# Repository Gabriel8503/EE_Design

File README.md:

# ⚡ EE_Design

Welcome to my Electrical Engineering design repository. This space is dedicated to documenting my journey as I build, test, and refine custom circuitry—from concept to production.

## 📘 Purpose

This repo will serve as a running log of my EE projects, experiments, and useful resources I reference or study during the process.

## 🛠️ Current Focus

- Designing microcontroller-based boards from scratch  
- Understanding and applying best practices in PCB design  
- Learning embedded systems and firmware workflows  

## 📚 Resources

Here's a curated list of resources that I'm currently using:

- **Getting to Blinky 5.0**  
  *(A foundational project series for FPGA and PCB design by Chris Gammell)*

- **Building a Microcontroller Board from Scratch**  
  [PDF ](https://attachments.convertkitcdnm.com/131144/1861af26-d50b-4f31-98b9-467ac304307f/Building-a-Microcontroller-Board-from-Scratch.pdf?utm_campaign=Landing%20Page%20or%20Form%20-%20939283&utm_medium=email&utm_source=convertkit)  
  *(Comprehensive walkthrough of the full design-to-manufacturing pipeline)*

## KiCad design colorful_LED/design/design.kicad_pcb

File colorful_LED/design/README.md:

# PCB Design Documentation

## Schematic
Below is the latest schematic snapshot for reference:  

## PCB Layout
Below is the latest PCB layout snapshot for reference:

### Front 

### Back

## Design Notes
- **Software Used:** KiCad  
- **Board Specs :**
  - Dimensions (mm): 66.5 x 60
  - Layer count: 4
  - Power requirements: 3V Cell Battery / USB

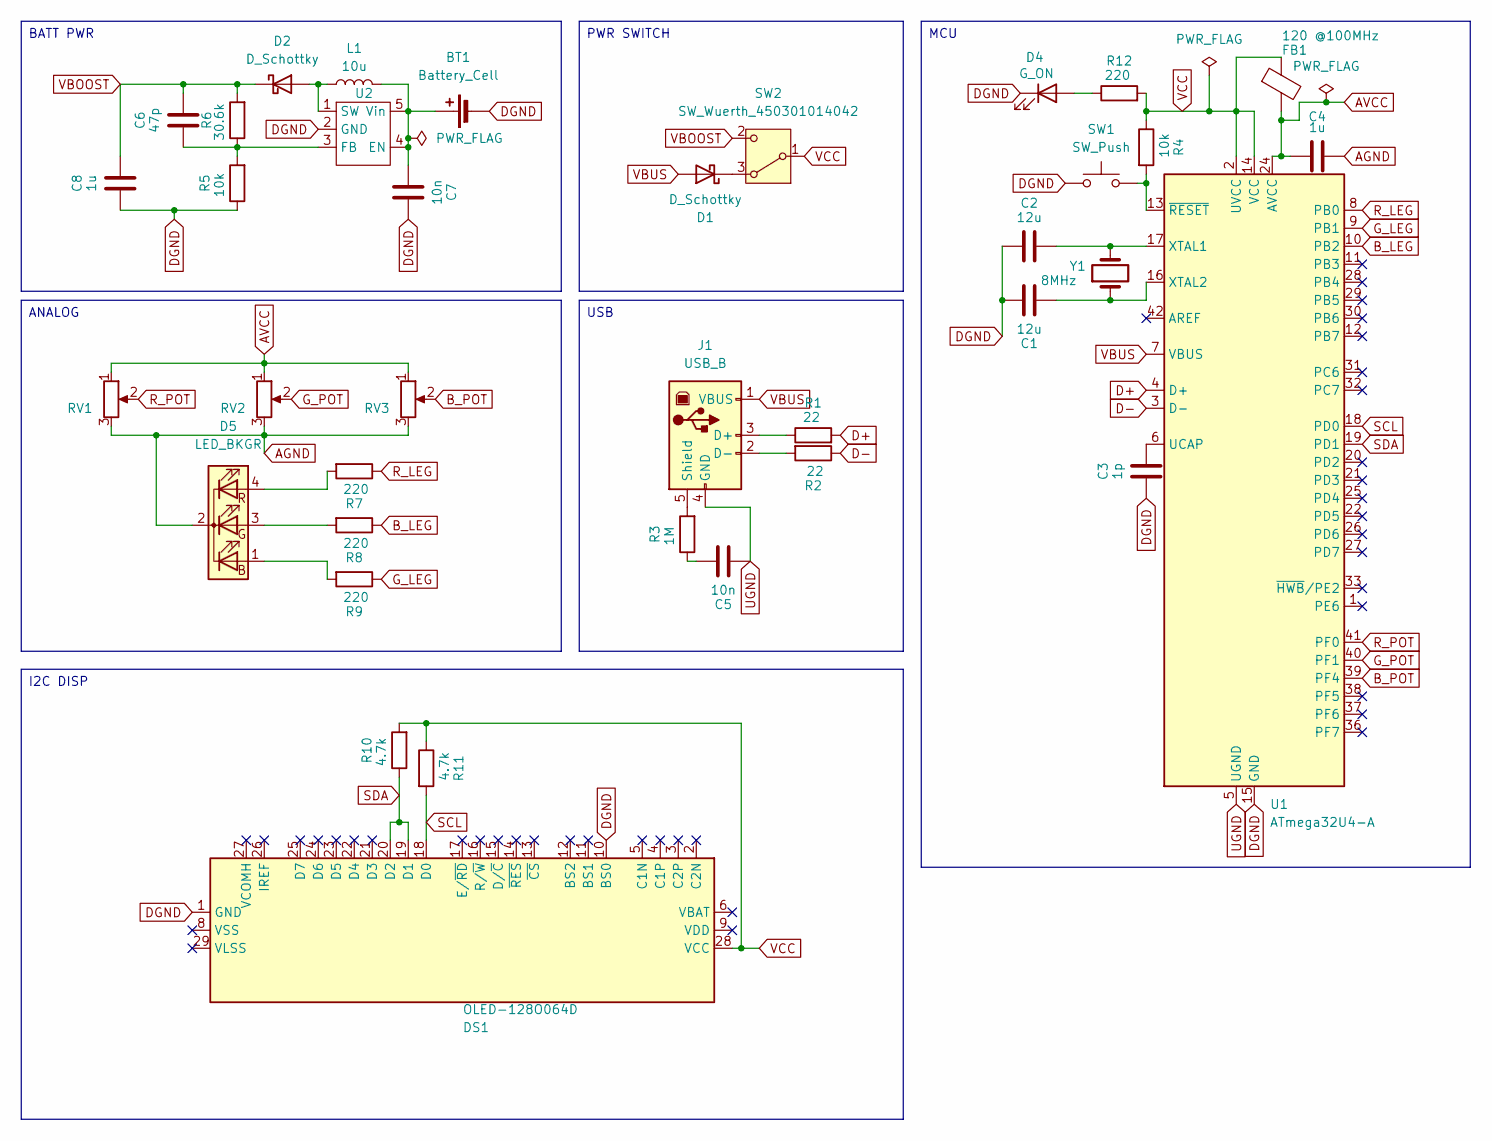
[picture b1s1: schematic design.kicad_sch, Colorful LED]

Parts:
BT1: Battery_Cell; BatteryHolder_ComfortableElectronic_CH273-2450_1x2450
C1, C2: 12u; C_0805_2012Metric
C3: 1p; C_0805_2012Metric
C4, C8: 1u; C_0805_2012Metric
C5, C7: 10n; C_0805_2012Metric
C6: 47p; C_0805_2012Metric
D1, D2: D_Schottky; D_0805_2012Metric
D4: G_ON; LED_0805_2012Metric
D5: LED_BKGR; LED_D5.0mm-4_RGB
DS1: OLED-128O064D
FB1: 120 @100MHz; L_0603_1608Metric_Pad1.05x0.95mm_HandSolder
J1: USB_B; USB_B_Lumberg_2411_02_Horizontal
L1: 10u; L_0805_2012Metric
R1, R2: 22; R_0805_2012Metric
R3: 1M; R_0805_2012Metric
R4, R5: 10k; R_0805_2012Metric
R6: 30.6k; R_0805_2012Metric
R7, R8, R9, R12: 220; R_0805_2012Metric
R10, R11: 4.7k; R_0805_2012Metric
RV1, RV2, RV3: R_Potentiometer; Potentiometer_Bourns_3314S_Horizontal
SW1: SW_Push; SW_Push_1TS009xxxx-xxxx-xxxx_6x6x5mm
SW2: SW_Wuerth_450301014042; SW_Slide-03_Wuerth-WS-SLTV_10x2.5x6.4_P2.54mm
U1: ATmega32U4-A; TQFP-44_10x10mm_P0.8mm
U2: Reg
Y1: 8MHz; Crystal_SMD_HC49-SD_HandSoldering

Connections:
AGND: C4.1, D5.2 (K), RV1.3, RV2.3, RV3.3
AVCC: C4.2, FB1.2, RV1.1, RV2.1, RV3.1, U1.24 (AVCC), U1.44 (AVCC)
B_LEG: R8.1, U1.10 (PB2)
B_POT: RV3.2, U1.39 (PF4)
D+: R1.2, U1.4 (D+)
D-: R2.1, U1.3 (D-)
DGND: BT1.2 (-), C1.1, C2.1, C3.2, C7.1, C8.2, D4.1 (K), DS1.1 (GND), DS1.10 (BS0), DS1.30 (GND), R5.1, SW1.1, U1.15 (GND), U1.23 (GND), U1.35 (GND), U1.43 (GND), U2.2 (GND)
G_LEG: R9.1, U1.9 (PB1)
G_POT: RV2.2, U1.40 (PF1)
unnamed: BT1.1 (+), C7.2, L1.2, U2.4 (EN), U2.5 (Vin)
unnamed: C5.1, R3.1
unnamed: D1.1 (K), SW2.3 (A)
unnamed: D2.2 (A), L1.1, U2.1 (SW)
unnamed: D4.2 (A), R12.1
unnamed: D5.1 (BA), R9.2
unnamed: D5.3 (GA), R8.2
unnamed: D5.4 (RA), R7.2
unnamed: J1.3 (D+), R1.1
unnamed: J1.2 (D-), R2.2
unnamed: J1.5 (Shield), R3.2
unnamed: C3.1, U1.6 (UCAP)
unnamed: C2.2, U1.17 (XTAL1), Y1.2
unnamed: C1.2, U1.16 (XTAL2), Y1.1
unnamed: R4.2, SW1.2, U1.13 (~RESET)
unnamed: C6.2, R5.2, R6.1, U2.3 (FB)
R_LEG: R7.1, U1.8 (PB0)
R_POT: RV1.2, U1.41 (PF0)
SCL: DS1.18 (D0), R11.2, U1.18 (PD0)
SDA: DS1.19 (D1), DS1.20 (D2), R10.1, U1.19 (PD1)
UGND: C5.2, J1.4 (GND), U1.5 (UGND)
VBOOST: C6.1, C8.1, D2.1 (K), R6.2, SW2.2 (C)
VBUS: D1.2 (A), J1.1 (VBUS), U1.7 (VBUS)
VCC: DS1.28 (VCC), FB1.1, R4.1, R10.2, R11.1, R12.2, SW2.1 (B), U1.2 (UVCC), U1.14 (VCC), U1.34 (VCC)

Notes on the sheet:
BATT PWR
I2C DISP
PWR SWITCH
ANALOG
USB
MCU

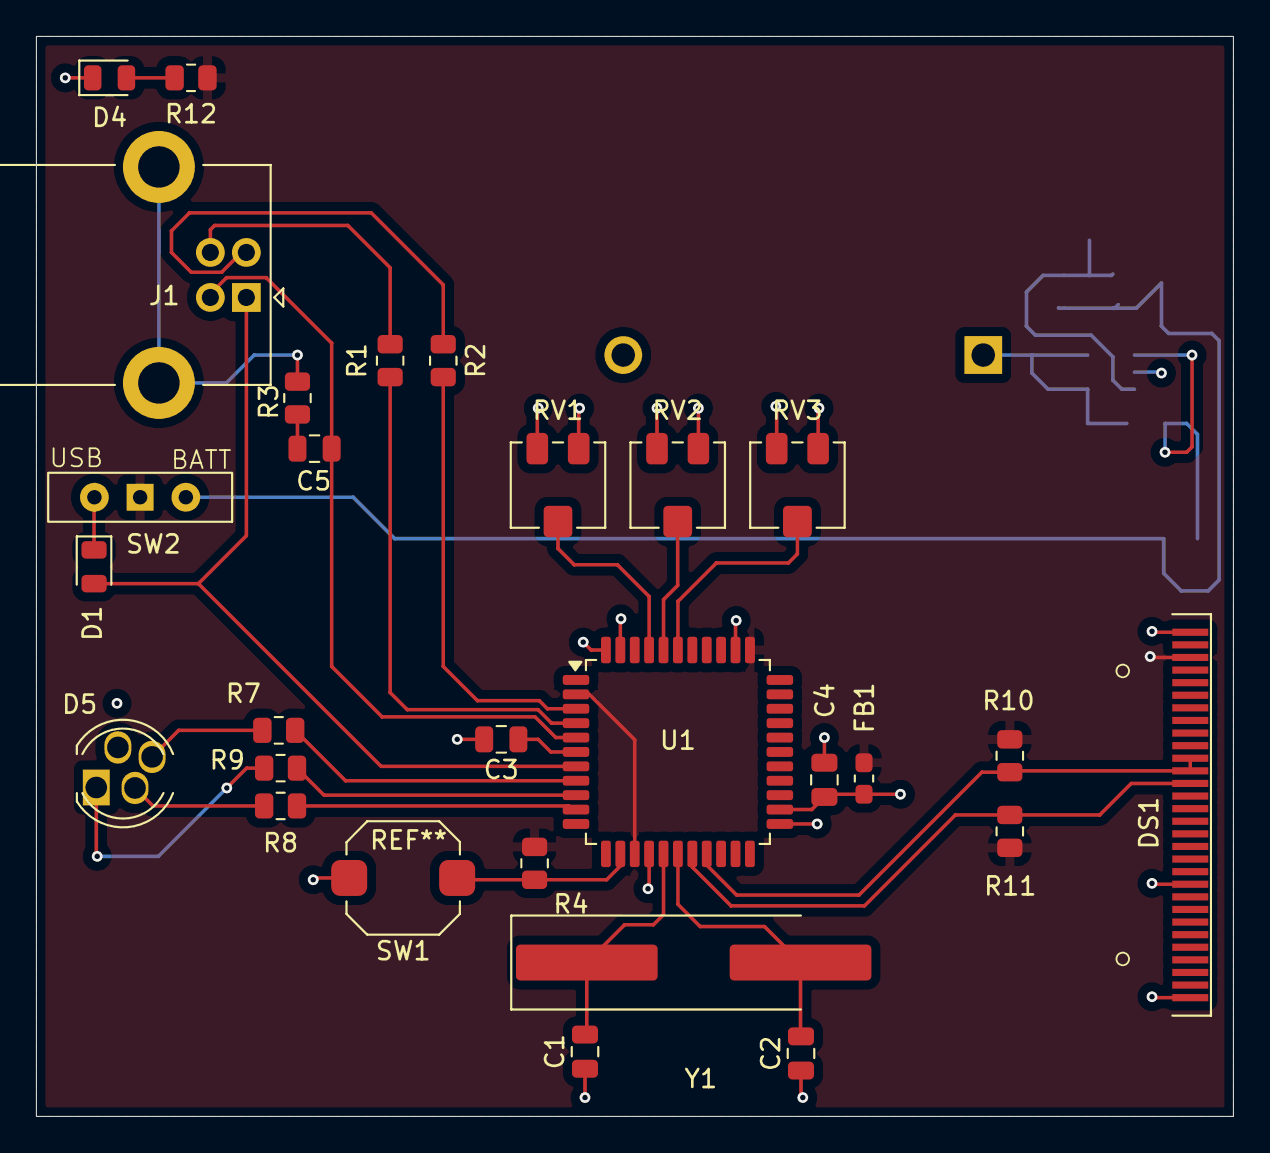
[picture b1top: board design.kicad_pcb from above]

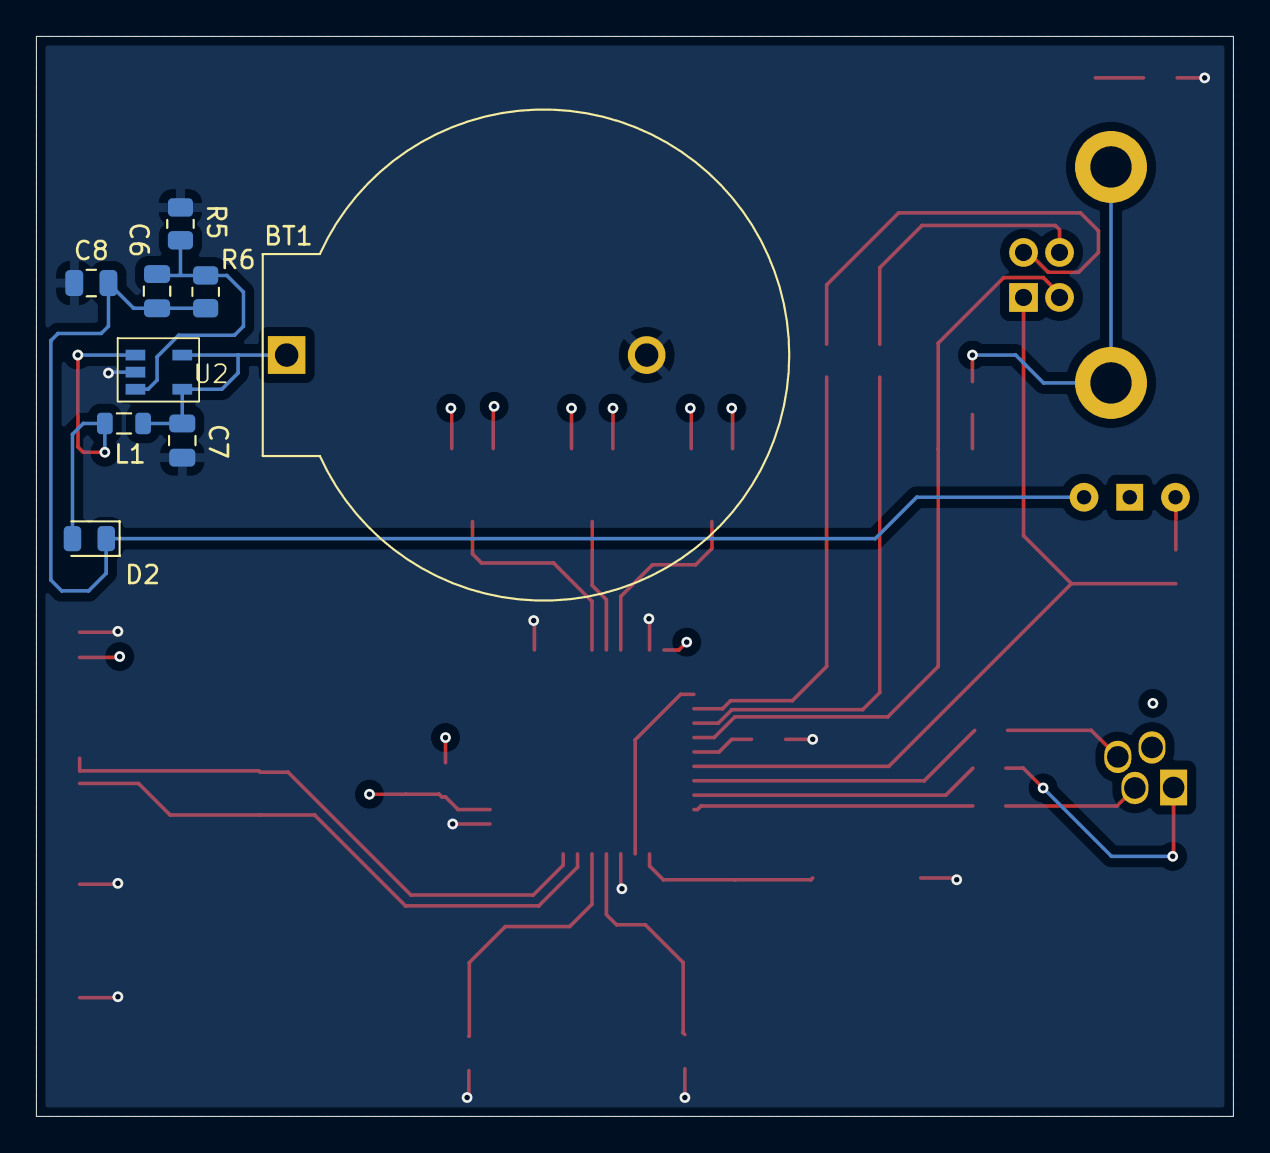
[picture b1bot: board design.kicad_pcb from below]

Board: 4 copper layers, 66.5 x 60.0 mm, 37 parts (9 on the bottom side), 33 nets.

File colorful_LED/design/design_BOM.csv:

"Reference","Qty","Value","DNP","Exclude from BOM","Exclude from Board","Footprint","Datasheet"
"BT1","1","Battery_Cell","","","","Battery:BatteryHolder_ComfortableElectronic_CH273-2450_1x2450","~"
"C1,C2","2","12u","","","","","~"
"C3","1","1p","","","","Capacitor_SMD:C_0805_2012Metric","~"
"C4,C8","2","1u","","","","Capacitor_SMD:C_0805_2012Metric","~"
"C5,C7","2","10n","","","","Capacitor_SMD:C_0805_2012Metric","~"
"C6","1","47p","","","","Capacitor_SMD:C_0805_2012Metric","~"
"D1,D2","2","D_Schottky","","","","Diode_SMD:D_0805_2012Metric","~"
"D4","1","G_ON","","","","LED_SMD:LED_0805_2012Metric","~"
"D5","1","LED_BKGR","","","","LED_THT:LED_D5.0mm-4_RGB","~"
"DS1","1","OLED-128O064D","","","","Display:OLED-128O064D","https://www.vishay.com/docs/37902/oled128o064dbpp3n00000.pdf"
"FB1","1","120 @100MHz","","","","Inductor_SMD:L_0603_1608Metric_Pad1.05x0.95mm_HandSolder","~"
"J1","1","USB_B","","","","Connector_USB:USB_B_Lumberg_2411_02_Horizontal","~"
"L1","1","L","","","","Inductor_SMD:L_0805_2012Metric","~"
"R1,R2","2","22","","","","Resistor_SMD:R_0805_2012Metric","~"
"R3","1","1M","","","","Resistor_SMD:R_0805_2012Metric","~"
"R4,R5","2","10k","","","","Resistor_SMD:R_0805_2012Metric","~"
"R6","1","30.6k","","","","Resistor_SMD:R_0805_2012Metric","~"
"R7,R8,R9,R12","4","220","","","","Resistor_SMD:R_0805_2012Metric","~"
"R10,R11","2","4.7k","","","","Resistor_SMD:R_0805_2012Metric","~"
"RV1,RV2,RV3","3","R_Potentiometer","","","","Potentiometer_SMD:Potentiometer_ACP_CA6-VSMD_Vertical","~"
"SW1","1","SW_Push","","","","Button_Switch_SMD:SW_Push_1TS009xxxx-xxxx-xxxx_6x6x5mm","~"
"SW2","1","SW_Wuerth_450301014042","","","","Button_Switch_THT:SW_Slide-03_Wuerth-WS-SLTV_10x2.5x6.4_P2.54mm","https://www.we-online.com/components/products/datasheet/4503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"
"U1","1","ATmega32U4-A","","","","Package_QFP:TQFP-44_10x10mm_P0.8mm","http://ww1.microchip.com/downloads/en/DeviceDoc/Atmel-7766-8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"
"U2","1","~","","","","Colorful_LED:Reg",""
"Y1","1","8MHz","","","","Crystal:Crystal_SMD_HC49-SD_HandSoldering","~"

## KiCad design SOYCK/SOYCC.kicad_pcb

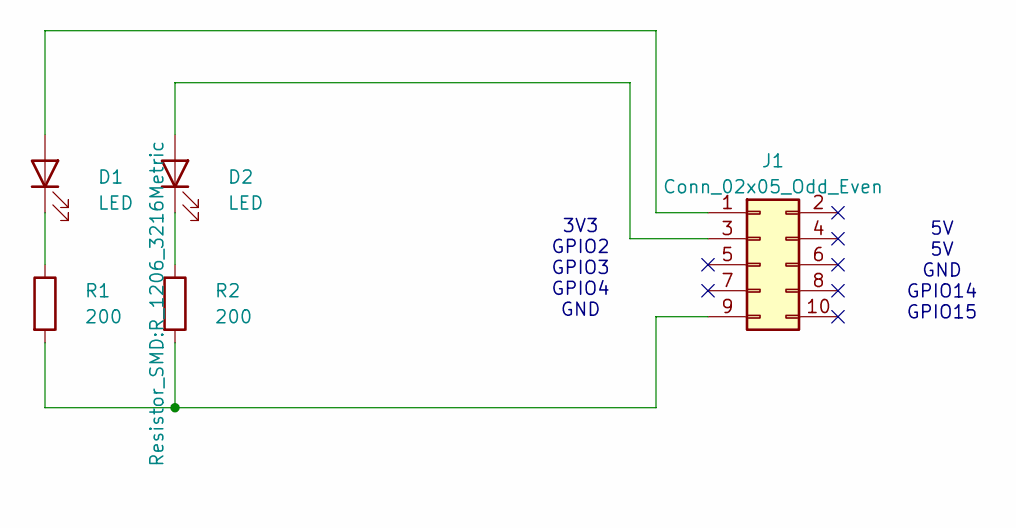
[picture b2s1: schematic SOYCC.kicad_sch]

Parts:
D1, D2: LED; LED_1206_3216Metric
J1: Conn_02x05_Odd_Even; PinHeader_2x05_P1.00mm_Vertical
R1: 200; R_0612_1632Metric
R2: 200; R_1206_3216Metric

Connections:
unnamed: D1.2 (A), J1.1
unnamed: D1.1 (K), R1.1
unnamed: D2.2 (A), J1.3
unnamed: D2.1 (K), R2.1
unnamed: J1.9, R1.2, R2.2

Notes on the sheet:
5V 5V GND GPIO14 GPIO15
3V3 GPIO2 GPIO3 GPIO4 GND

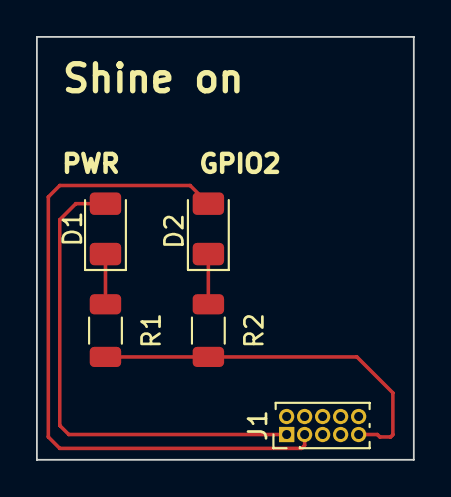
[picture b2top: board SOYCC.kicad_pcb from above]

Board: 2 copper layers, 20.9 x 23.5 mm, 5 parts (0 on the bottom side), 5 nets.

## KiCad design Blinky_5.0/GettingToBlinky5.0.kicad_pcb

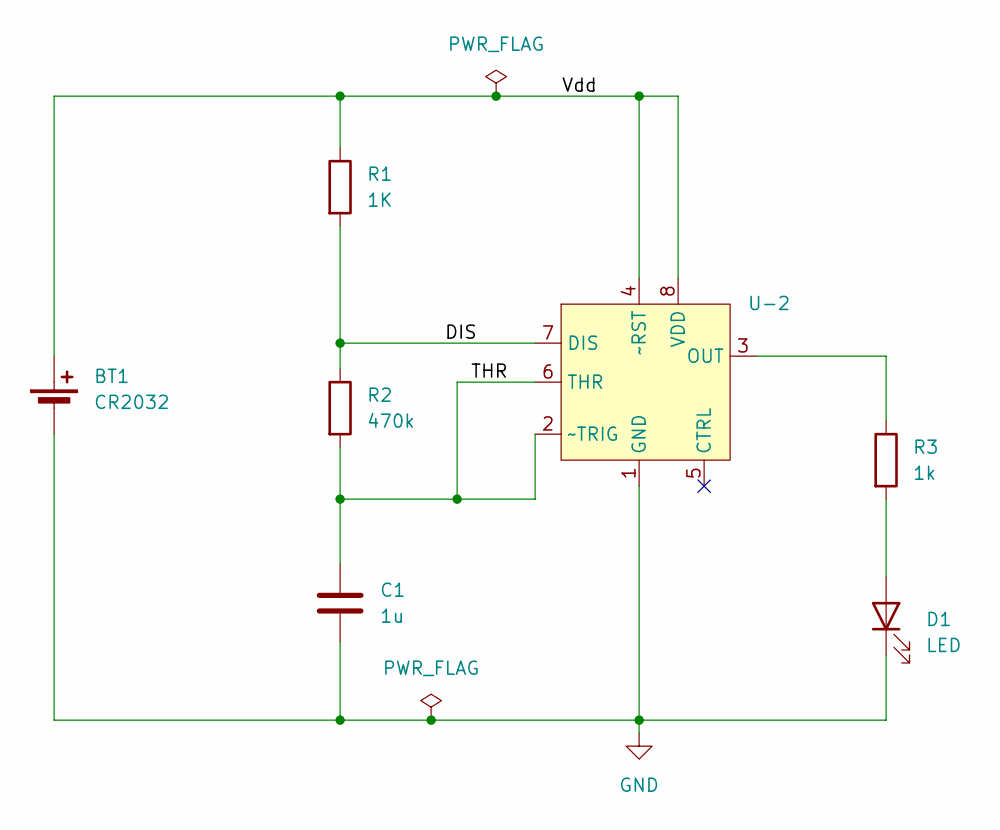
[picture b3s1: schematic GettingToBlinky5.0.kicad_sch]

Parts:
BT1: CR2032; C-Battery
C1: 1u; C_0805_2012Metric
D1: LED; LED_0805_2012Metric
R1: 1K; R_0805_2012Metric
R2: 470k; R_0805_2012Metric
R3: 1k; R_0805_2012Metric
U-2: SO-8_3.9x4.9mm_P1.27mm

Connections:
/DIS: R1.2, R2.1, U-2.7 (DIS)
/THR: C1.1, R2.2, U-2.2 (~TRIG), U-2.6 (THR)
/Vdd: BT1.1 (+), R1.1, U-2.4 (~RST), U-2.8 (VDD)
GND: BT1.2 (-), C1.2, D1.1 (K), U-2.1 (GND)
unnamed: D1.2 (A), R3.2
unnamed: R3.1, U-2.3 (OUT)

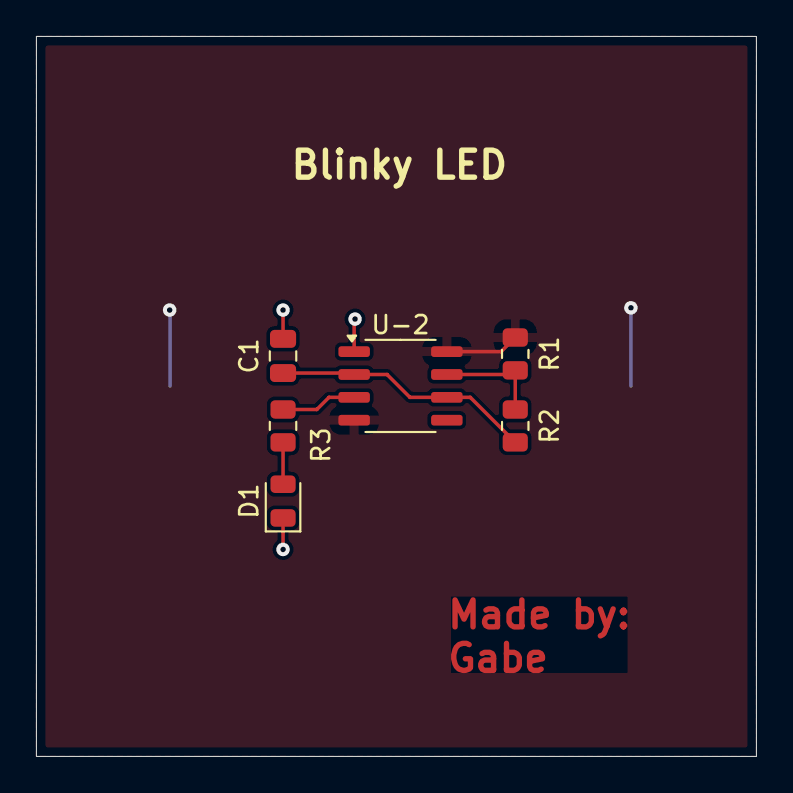
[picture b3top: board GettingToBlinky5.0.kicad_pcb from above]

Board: 2 copper layers, 40.0 x 40.0 mm, 7 parts (1 on the bottom side), 6 nets.

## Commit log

2025-07-01 added TODO list
2025-07-01 Getting Started
2025-07-02 Started Project
2025-07-02 Added Schematic
2025-07-03 Made Custon Footprint
2025-07-03 PCB Edited
2025-07-06 fixed error with footprint of 7555
2025-07-06 Just resetting I messed up somewhere?
2025-07-09 No errors generating gerber
2025-07-09 Forgot to hit save
2025-07-10 Vias were too small
2025-07-10 Gerbers
2025-07-10 Gerbers 2.0
2025-07-16 New Project
2025-07-16 Update README.md
    made documentation for README
2025-07-19 made simulation directory
2025-07-19 fixed merge again
2025-07-22 Started Circuit Diagram
2025-07-22 Added some footprints
2025-07-24 worked on schematic and added boost converter to custom lib
2025-07-26 Finished analog
2025-07-27 Finished Schematic
2025-08-07 Added last footprint tht
2025-08-07 Fixed some minor bugs
2025-08-08 added components
2025-08-14 Put PCB Components near each other, want to reduce size and route traces
2025-08-14 Create README.md
    add readme to design
2025-08-14 Update README.md
    image fix?
2025-08-14 Added .gitignore
2025-08-18 traces etched
2025-08-18 pictures
2025-12-09 controls project
